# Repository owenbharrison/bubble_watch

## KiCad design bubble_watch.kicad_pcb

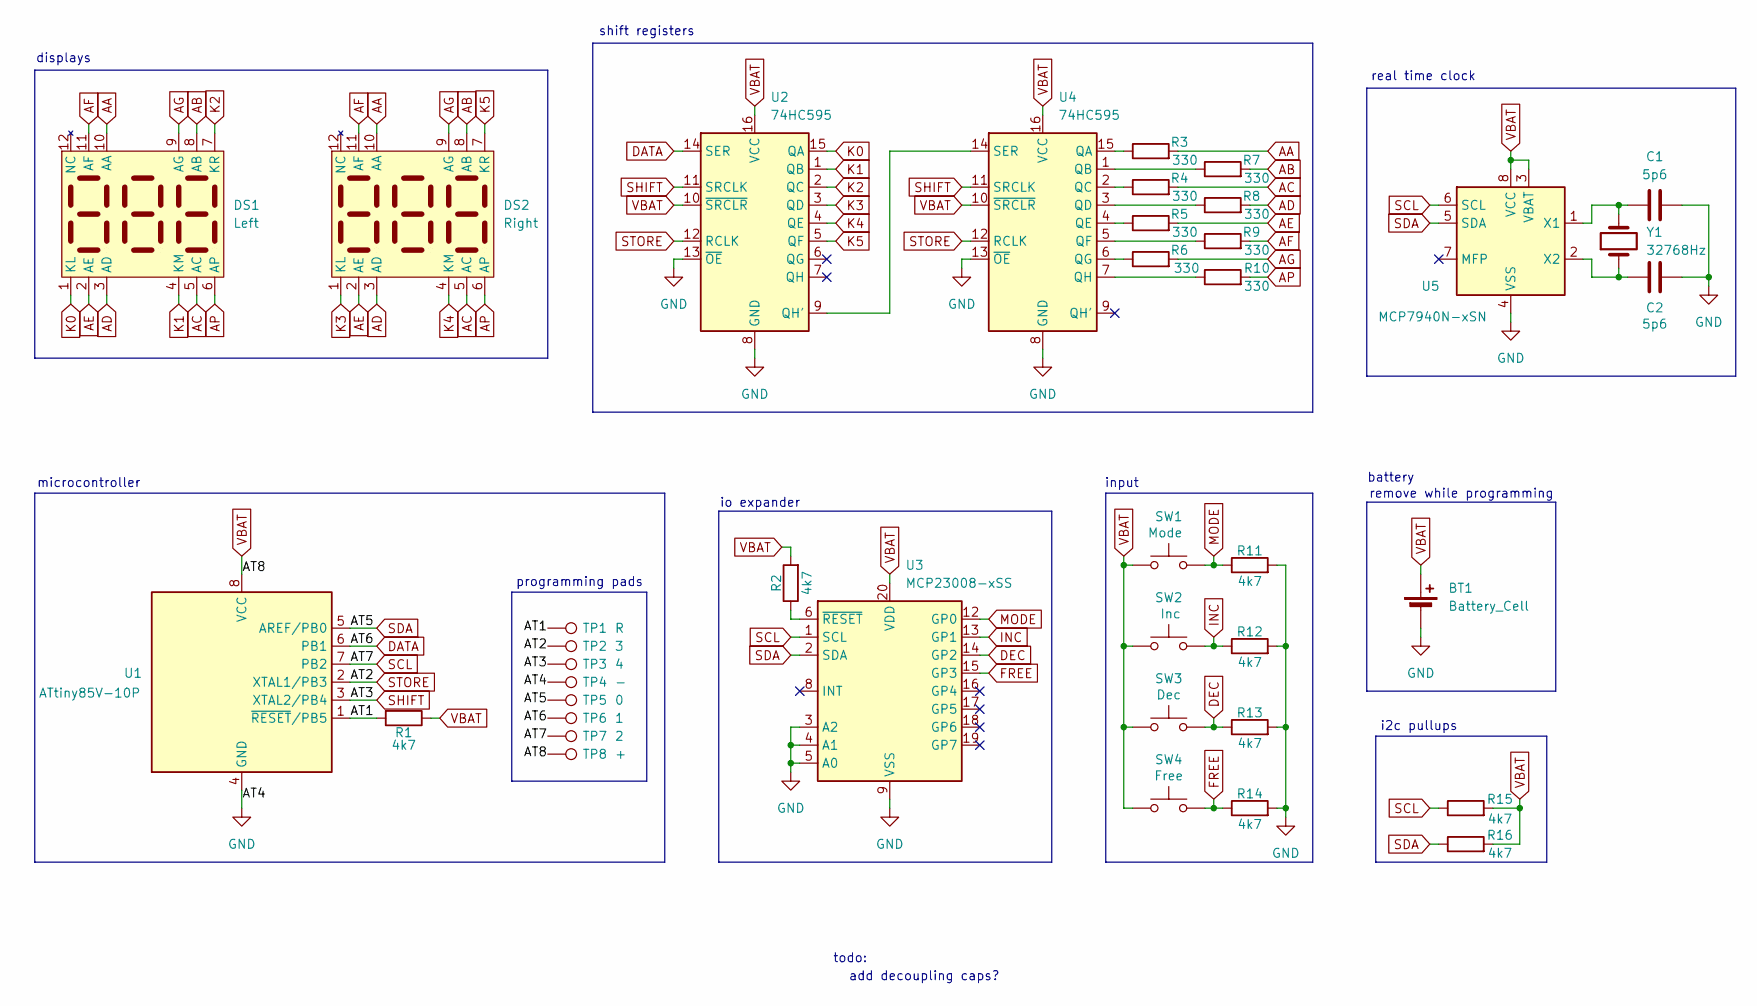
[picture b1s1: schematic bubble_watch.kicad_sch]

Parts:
BT1: Battery_Cell; BatteryHolder_Multicomp_BC-2001_1x2032
C1, C2: 5p6; C_0603_1608Metric
DS1: Left; BUBBLE3
DS2: Right; BUBBLE3
R1, R2, R11, R12, R13, R14, R15, R16: 4k7; R_0603_1608Metric
R3, R4, R5, R6, R7, R8, R9, R10: 330; R_0603_1608Metric
SW1: Mode; SW_Push_1P1T_NO_E-Switch_TL3301NxxxxxG
SW2: Inc; SW_Push_1P1T_NO_E-Switch_TL3301NxxxxxG
SW3: Dec; SW_Push_1P1T_NO_E-Switch_TL3301NxxxxxG
SW4: Free; SW_Push_1P1T_NO_E-Switch_TL3301NxxxxxG
TP1: R; TestPoint_Pad_D1.5mm
TP2: 3; TestPoint_Pad_D1.5mm
TP3: 4; TestPoint_Pad_D1.5mm
TP4: -; TestPoint_Pad_D1.5mm
TP5: 0; TestPoint_Pad_D1.5mm
TP6: 1; TestPoint_Pad_D1.5mm
TP7: 2; TestPoint_Pad_D1.5mm
TP8: +; TestPoint_Pad_D1.5mm
U1: ATtiny85V-10P; SOIC-8_3.9x4.9mm_P1.27mm
U2, U4: 74HC595; TSSOP-16_4.4x5mm_P0.65mm
U3: MCP23008-xSS; SSOP-20_5.3x7.2mm_P0.65mm
U5: MCP7940N-xSN; SOIC-8_3.9x4.9mm_P1.27mm
Y1: 32768Hz; Crystal_DS26_D2.0mm_L6.0mm_Horizontal

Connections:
/AT1: R1.2, TP1.1 (1_1), U1.1 (~RESET/PB5)
AA: DS1.10 (AA), DS2.10 (AA), R3.2
AB: DS1.8 (AB), DS2.8 (AB), R7.2
AC: DS1.5 (AC), DS2.5 (AC), R4.2
AD: DS1.3 (AD), DS2.3 (AD), R8.2
AE: DS1.2 (AE), DS2.2 (AE), R5.2
AF: DS1.11 (AF), DS2.11 (AF), R9.2
AG: DS1.9 (AG), DS2.9 (AG), R6.2
AP: DS1.6 (AP), DS2.6 (AP), R10.2
DATA: TP6.1 (1_1), U1.6 (PB1), U2.14 (SER)
DEC: R13.1, SW3.2, U3.14 (GP2)
FREE: R14.1, SW4.2, U3.15 (GP3)
GND: BT1.2 (-), C1.2, C2.1, R11.2, R12.2, R13.2, R14.2, TP4.1 (1_1), U1.4 (GND), U2.8 (GND), U2.13 (~OE), U3.3 (A2), U3.4 (A1), U3.5 (A0), U3.9 (VSS), U4.8 (GND), U4.13 (~OE), U5.4 (VSS)
INC: R12.1, SW2.2, U3.13 (GP1)
K0: DS1.1 (KL), U2.15 (QA)
K1: DS1.4 (KM), U2.1 (QB)
K2: DS1.7 (KR), U2.2 (QC)
K3: DS2.1 (KL), U2.3 (QD)
K4: DS2.4 (KM), U2.4 (QE)
K5: DS2.7 (KR), U2.5 (QF)
MODE: R11.1, SW1.2, U3.12 (GP0)
unnamed: U2.9 (QH'), U4.14 (SER)
unnamed: R2.1, U3.6 (~RESET)
unnamed: R3.1, U4.15 (QA)
unnamed: R7.1, U4.1 (QB)
unnamed: R4.1, U4.2 (QC)
unnamed: R8.1, U4.3 (QD)
unnamed: R5.1, U4.4 (QE)
unnamed: R9.1, U4.5 (QF)
unnamed: R6.1, U4.6 (QG)
unnamed: R10.1, U4.7 (QH)
unnamed: C1.1, U5.1 (X1), Y1.2
unnamed: C2.2, U5.2 (X2), Y1.1
SCL: R15.1, TP7.1 (1_1), U1.7 (PB2), U3.1 (SCL), U5.6 (SCL)
SDA: R16.1, TP5.1 (1_1), U1.5 (AREF/PB0), U3.2 (SDA), U5.5 (SDA)
SHIFT: TP3.1 (1_1), U1.3 (XTAL2/PB4), U2.11 (SRCLK), U4.11 (SRCLK)
STORE: TP2.1 (1_1), U1.2 (XTAL1/PB3), U2.12 (RCLK), U4.12 (RCLK)
VBAT: BT1.1 (+), R1.1, R2.2, R15.2, R16.2, SW1.1, SW2.1, SW3.1, SW4.1, TP8.1 (1_1), U1.8 (VCC), U2.10 (~SRCLR), U2.16 (VCC), U3.20 (VDD), U4.10 (~SRCLR), U4.16 (VCC), U5.3 (VBAT), U5.8 (VCC)

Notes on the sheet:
microcontroller
real time clock
programming pads
todo:
battery
io expander
i2c pullups
displays
add decoupling caps?
input
shift registers
remove while programming

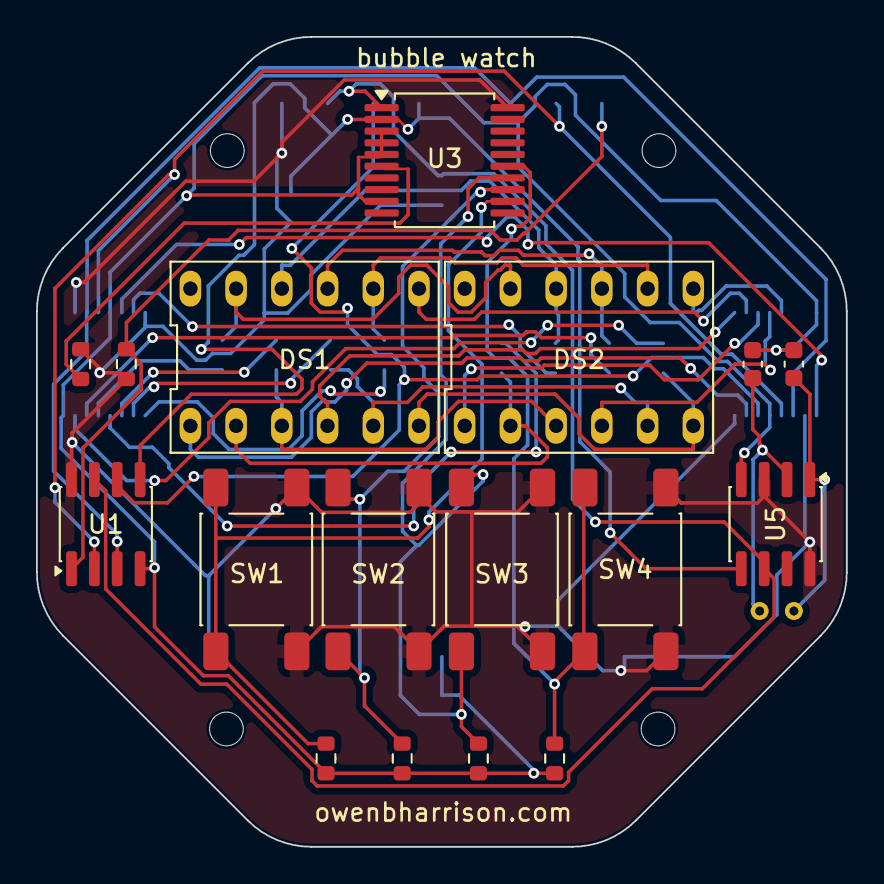
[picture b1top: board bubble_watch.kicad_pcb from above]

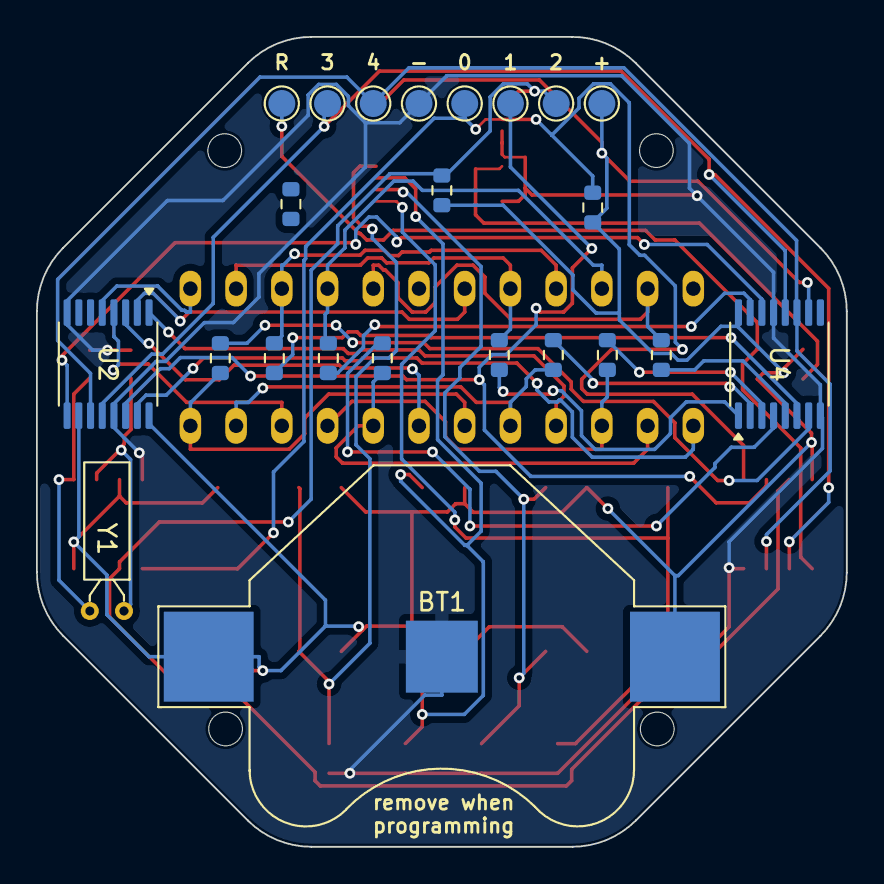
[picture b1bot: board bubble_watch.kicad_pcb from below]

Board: 2 copper layers, 45.0 x 45.0 mm, 40 parts (23 on the bottom side), 38 nets.

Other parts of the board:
R9#2: 4k7; R_0603_1608Metric
